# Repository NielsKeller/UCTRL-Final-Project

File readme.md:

# CMPE3815 Final Project: X-Y Oscilloscope Drawer

CMPE 3815, Microcontroller Systems\
Niels Keller\
Samuel Starzec

## Overview

The goal of this project was to have a microcontroller use an oscilloscope's X-Y mode to display Lissajous figures. The first stretch goal was to have the oscilloscope display more geometric shapes. The second stretch goal was design and fabricate a functioning PCB. Both stretch goals were met. As this is a final project for a class, a copy of each report has been included.

## Important Files

* Circuit schematic &rarr; Images/Circuit.png
* PCB files (KiCad) &rarr; PCB
* Arduino Library &rarr; ScopeXY.zip
* Final Reports &rarr; Reports

## Hardware Components

* Arduino UNO
* MCP4725 DAC (x2)
* PCB
* Bluetooth JDY-16 BLE Module

## Basic Documentation

    XYscope(int AddressX, int AddressY);

Constructor of the XYscope class.<br>
Parameters:

* int AddressX &rarr; I2C address of X DAC
* int AddressY &rarr; I2C address of Y DAC

##

    void dacSend(int address, int value);

Send output value to the DAC.<br>
Parameters:

* int address &rarr; I2C address of DAC
* int value &rarr; 0 - 4096 value to set output to

##

    void LJFigure(float ratio, float phase, int index, float fdiv);

Display Lissajous curve.<br>
Parameters:

* float ratio &rarr; Ratio between frequencies
* float phase &rarr; Phase offset ($\pi$ * radians)
* int index &rarr; Index on the sinusoid. Controls the input value
* float fdiv &rarr; Speed modifier $\approx$ 0.01 . Should be roughly the same for most figures for each scope.

##

    void LJFigureMoving(float ratio, float period, int index, float fdiv);

Display moving Lissajous curve.<br>
Parameters:

* float ratio &rarr; Ratio between frequencies
* float period &rarr; Period in seconds
* int index &rarr; Index on the sinusoid. Controls the input value
* float fdiv &rarr; Speed modifier: Should be roughly the same for most figures for each scope.

##

    void lineSc(int x1, int x2, int y1, int y2, long pts);

Maps lines from a 1000x1000 plane to the osiloscope and displays them.<br>
Parameters:

* int x1 &rarr; First x point
* int x2 &rarr; Second x point
* int y1 &rarr; First y point
* int y2 &rarr; Second y point
* long pts &rarr; Total number of points to plot

## Images

Unfortunately only display properly on GitHub.<br>
https://github.com/NielsKeller/ScopeXY

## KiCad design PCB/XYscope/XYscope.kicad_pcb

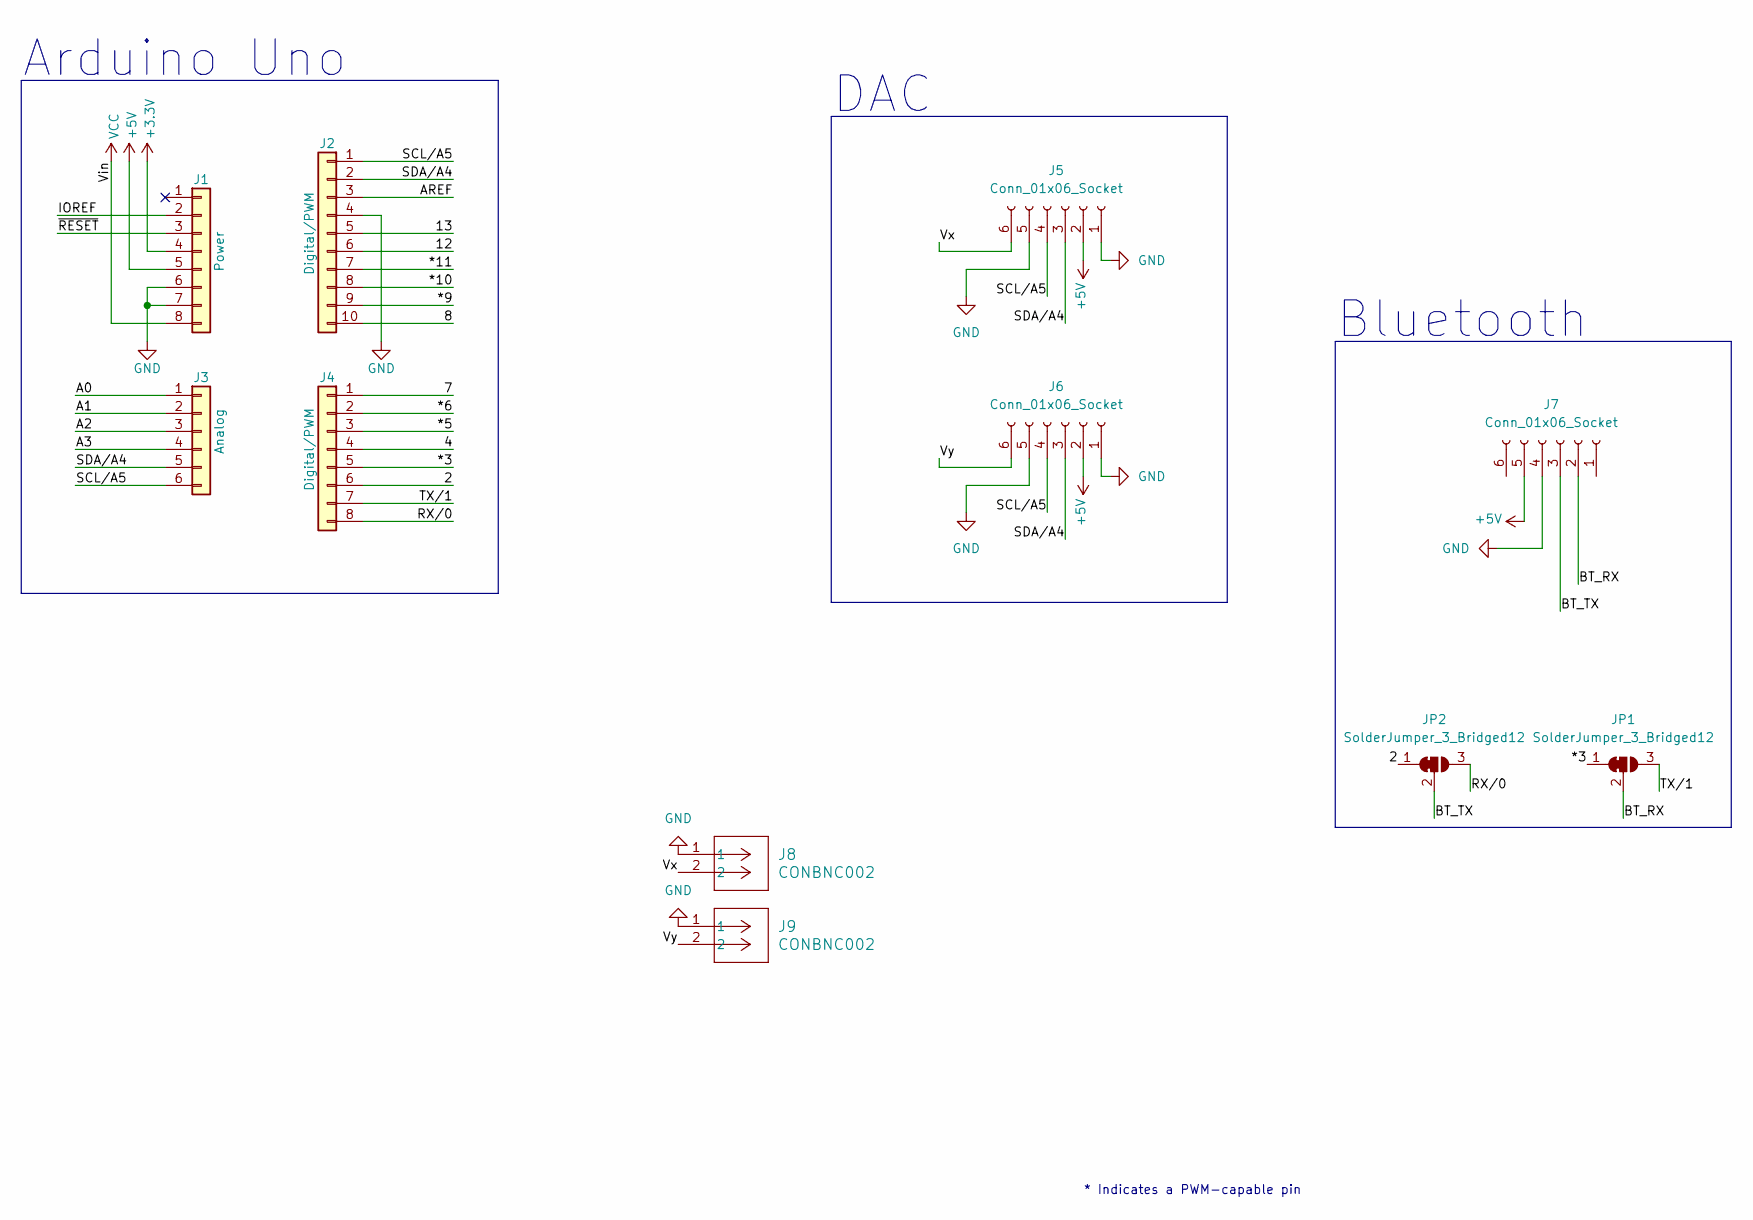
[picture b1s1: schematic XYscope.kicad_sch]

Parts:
J1: Power; PinSocket_1x08_P2.54mm_Vertical
J2: Digital/PWM; PinSocket_1x10_P2.54mm_Vertical
J3: Analog; PinSocket_1x06_P2.54mm_Vertical
J4: Digital/PWM; PinSocket_1x08_P2.54mm_Vertical
J5, J6, J7: Conn_01x06_Socket; PinSocket_1x06_P2.54mm_Vertical
J8, J9: CONBNC002; CONN_CONBN_LNX
JP1, JP2: SolderJumper_3_Bridged12; SolderJumper-3_P1.3mm_Bridged12_RoundedPad1.0x1.5mm

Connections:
+3V3: J1.4
+5V: J1.5, J5.2, J6.2, J7.5
/2: J4.6, JP2.1 (A)
/4: J4.4
/7: J4.1
/8: J2.10
/12: J2.6
/13: J2.5
/*3: J4.5, JP1.1 (A)
/*5: J4.3
/*6: J4.2
/*9: J2.9
/*10: J2.8
/*11: J2.7
/A0: J3.1
/A1: J3.2
/A2: J3.3
/A3: J3.4
/AREF: J2.3
/BT_RX: J7.2, JP1.2 (C)
/BT_TX: J7.3, JP2.2 (C)
/IOREF: J1.2
/RX/0: J4.8, JP2.3 (B)
/SCL/A5: J2.1, J3.6, J5.4, J6.4
/SDA/A4: J2.2, J3.5, J5.3, J6.3
/TX/1: J4.7, JP1.3 (B)
/Vx: J5.6, J8.2
/Vy: J6.6, J9.2
/~RESET: J1.3
GND: J1.6, J1.7, J2.4, J5.1, J5.5, J6.1, J6.5, J7.4, J8.1, J9.1
VCC: J1.8

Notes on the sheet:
Bluetooth
Arduino Uno
DAC
* Indicates a PWM-capable pin

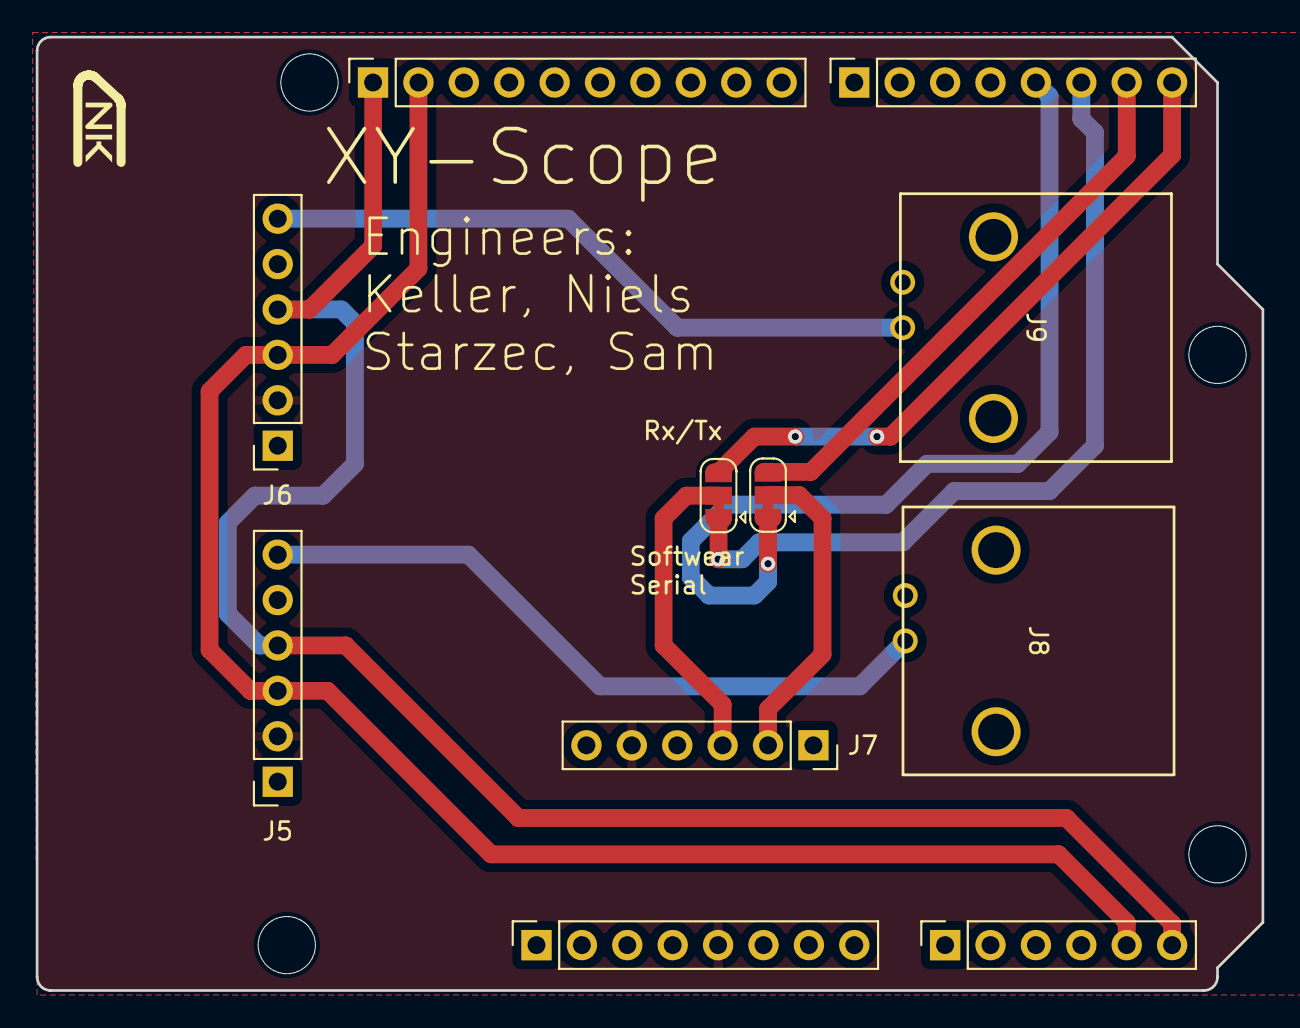
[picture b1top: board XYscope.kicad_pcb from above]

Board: 2 copper layers, 68.6 x 53.3 mm, 15 parts (0 on the bottom side), 12 nets.

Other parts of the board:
MH1, MH2, MH3, MH4: MountingHole_3.2mm

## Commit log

2024-11-13 Create DAC-Test.ino
    DAC test 1 from sample code
2024-11-13 testing change
2024-11-15 Updated to fix sin calculation
2024-11-19 Fixed a typo and made a new file that implements Bluetooth.
    The Bluetooth uses the RemoteXY app to add two sliders. One slider changes the ratio, and the other slider changes the phase.
2024-11-30 pcb work
2024-12-02 PCB update
2024-12-03 Created Arduino lib
2024-12-03 Bluetooth examples.
    The bluetooth_sliders file uses RemoteXY to change the phase and ration with sliders. The bluetooth_buttons file uses RemoteXY to have 3 buttons for 3 presets for the lissajous figure.
2024-12-03 Made Drawer program
2024-12-04 Fixed File Structure
2024-12-04 Created readme
2024-12-04 Added Photos for read me
2024-12-06 GeoDog
2024-12-06 Added presentation demo and moved files
2024-12-10 Updated read.me
    Updated the read me.
2024-12-10 Github image test
2024-12-10 Readme test 2
2024-12-10 Patched images
2024-12-10 Updated Bluetooth with geo dog.
    Added geo dog to the Bluetooth buttons example.
2024-12-10 Added pictures
2024-12-11 Uploaded report
2024-12-11 Fixed some readme issues
2024-12-11 Removed duplicate figure
2024-12-11 Added report info to readme
2024-12-11 removed example from example images
